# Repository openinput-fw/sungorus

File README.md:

# sungorus

Open source wireless mouse hardware.

## Specifications
- Wireless

## Firmware

sungorus is meant to run on [openinput](https://github.com/openinput-fw/openinput).

## Receiver

sungorus can work with the following *receivers:

- [russian-woodpecker](https://github.com/openinput-fw/russian-woodpecker) _(planned)_

`*provided they are running compatible firmware, typically openinput`

## License

This hardware is licensed under the [CERN-OHL-P v2](LICENSE) license.

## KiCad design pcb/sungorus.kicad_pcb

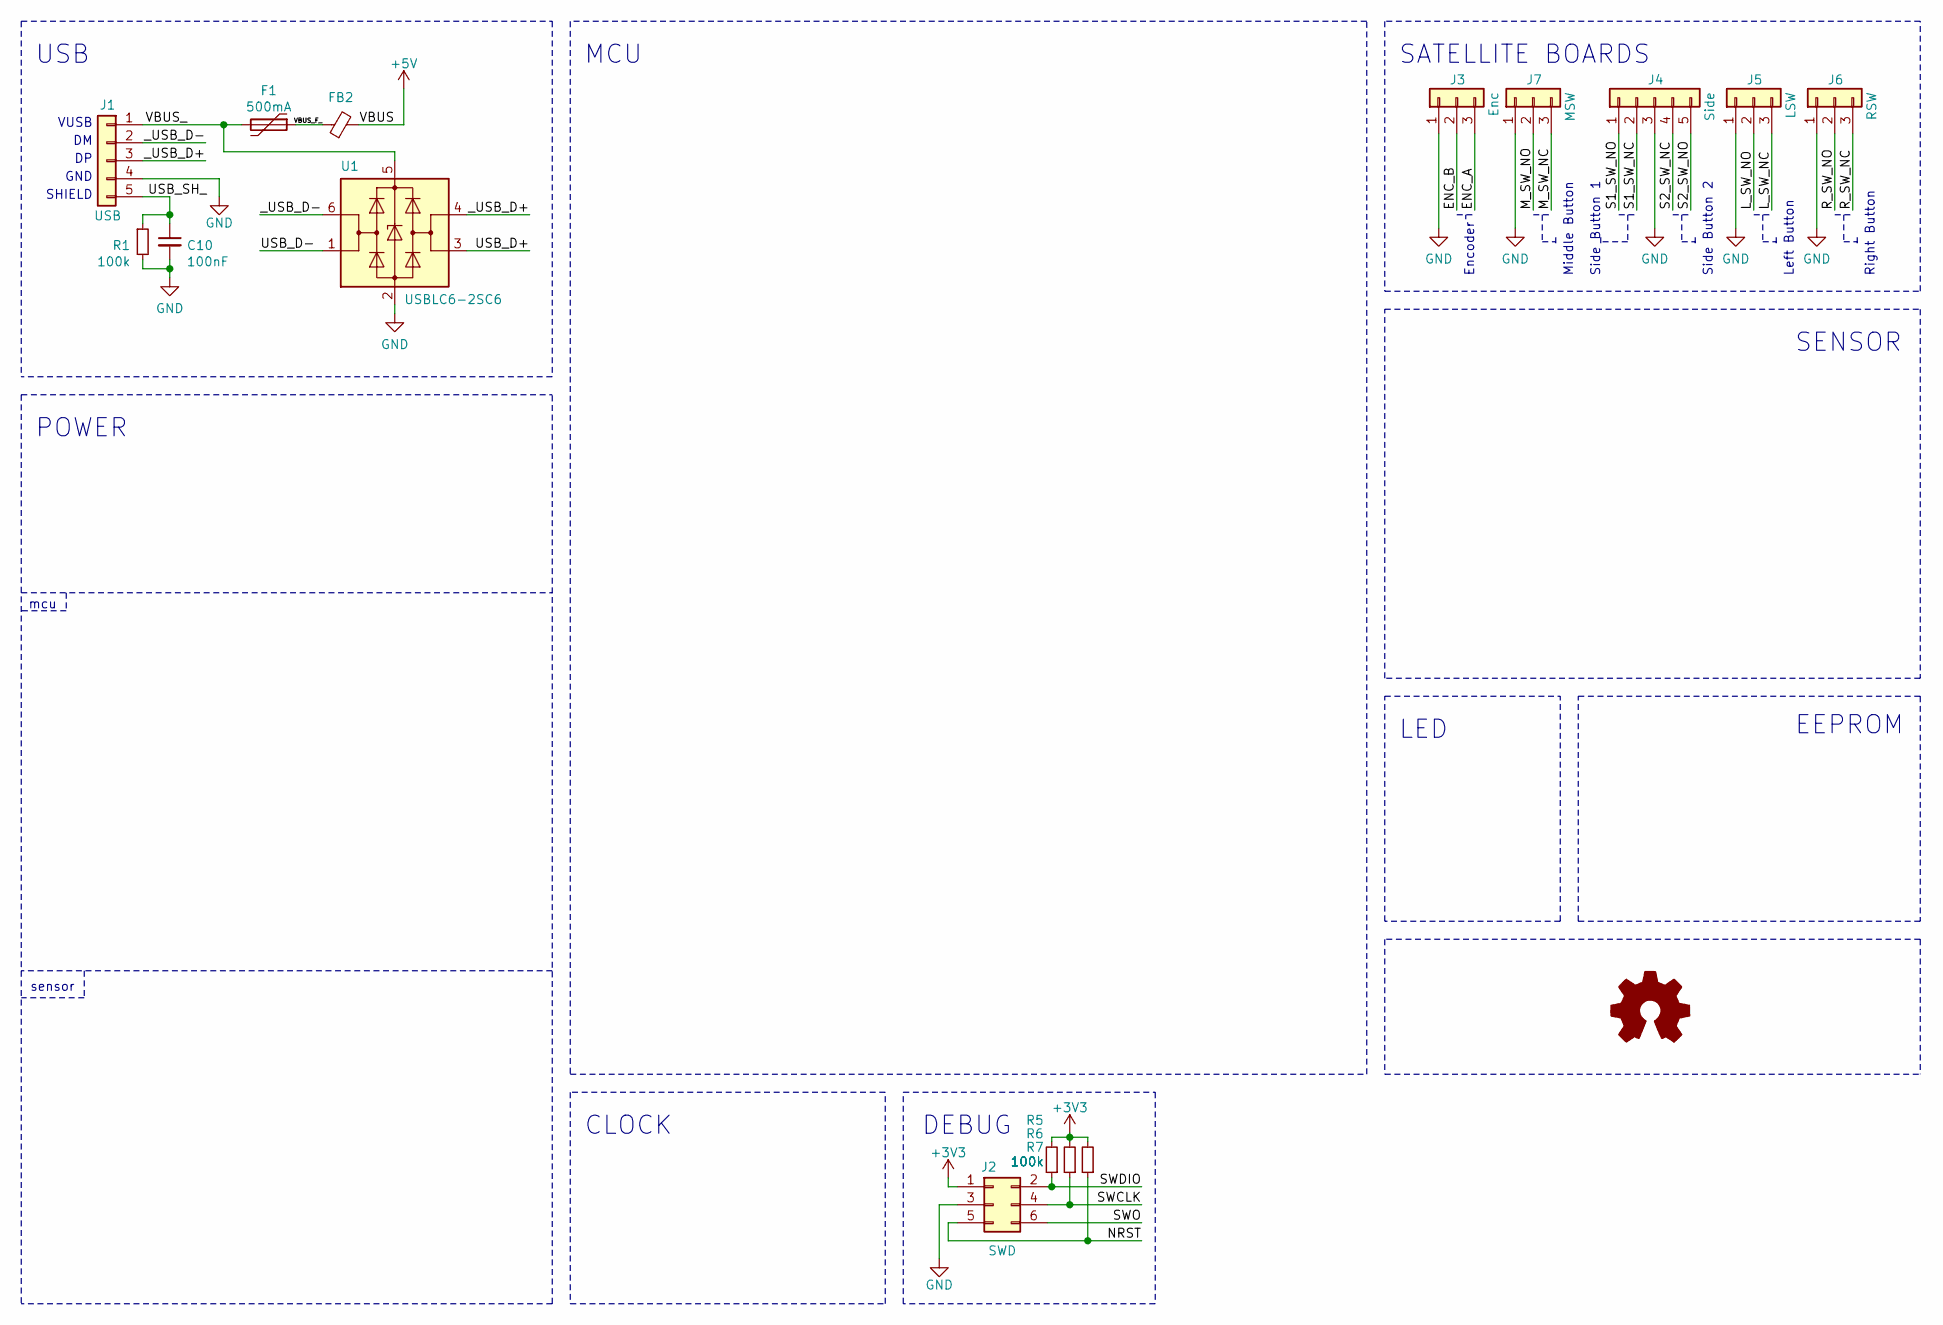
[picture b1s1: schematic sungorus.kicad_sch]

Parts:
C10: 100nF; C_0402_1005Metric
F1: 500mA; Fuse_0603_1608Metric_Castellated
FB2: L_0402_1005Metric
J1: USB; JST_PH_B5B-PH-K_1x05_P2.00mm_Vertical
J2: SWD; Tag-Connect_TC2030-IDC-NL_2x03_P1.27mm_Vertical
J3: Enc; JST_SH_BM03B-SRSS-TB_1x03-1MP_P1.00mm_Vertical
J4: Side; JST_SH_BM05B-SRSS-TB_1x05-1MP_P1.00mm_Vertical
J5: LSW; JST_SH_BM03B-SRSS-TB_1x03-1MP_P1.00mm_Vertical
J6: RSW; JST_SH_BM03B-SRSS-TB_1x03-1MP_P1.00mm_Vertical
J7: MSW; JST_SH_BM03B-SRSS-TB_1x03-1MP_P1.00mm_Vertical
R1, R5, R6, R7: 100k; R_0402_1005Metric
U1: USBLC6-2SC6; SOT-23-6

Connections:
+3V3: J2.1, R5.2, R6.2, R7.2
+5V: FB2.2
/ENC_A: J3.3
/ENC_B: J3.2
/L_SW_NC: J5.3
/L_SW_NO: J5.2
/M_SW_NC: J7.3
/M_SW_NO: J7.2
/NRST: J2.5, R7.1
/R_SW_NC: J6.3
/R_SW_NO: J6.2
/S1_SW_NC: J4.2
/S1_SW_NO: J4.1
/S2_SW_NC: J4.4
/S2_SW_NO: J4.5
/SWCLK: J2.4, R6.1
/SWDIO: J2.2, R5.1
/SWO: J2.6
/USB_D+: U1.3 (I/O2)
/USB_D-: U1.1 (I/O1)
/USB_SH_: C10.1, J1.5, R1.1
/VBUS_: F1.2, J1.1, U1.5 (VBUS)
/VBUS_F_: F1.1, FB2.1
/_USB_D+: J1.3, U1.4 (I/O2)
/_USB_D-: J1.2, U1.6 (I/O1)
GND: C10.2, J1.4, J2.3, J3.1, J4.3, J5.1, J6.1, J7.1, R1.2, U1.2 (GND)

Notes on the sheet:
Side Button 2
Left Button
DEBUG
USB
CLOCK
SENSOR
SHIELD
Right Button
VUSB
MCU
mcu
Side Button 1
GND
POWER
sensor
Encoder
Middle Button
SATELLITE BOARDS
LED
EEPROM

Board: 4 copper layers, 15 parts (0 on the bottom side), 10 nets, no tracks yet.

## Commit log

2021-11-25 readme: add project info
2021-11-25 license: license project under CERN-OHL-P v2
2021-11-25 docs: add barebones documentation for readthedocs
2021-11-25 pcb: add barebones pcb based on sammy r0.1
2021-11-25 pcb: add docs about labels

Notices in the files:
pcb/sungorus.kicad_pcb:
This source describes Open Hardware and is licensed under the CERN-OHL-Pv2
Copyright (c) Rafael Silva
